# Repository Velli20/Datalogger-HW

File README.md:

# Datalogger board design with KiCad
The design files are available and free to use. For Any project related question do not hesitate to message me.

## Board Layout 3D View

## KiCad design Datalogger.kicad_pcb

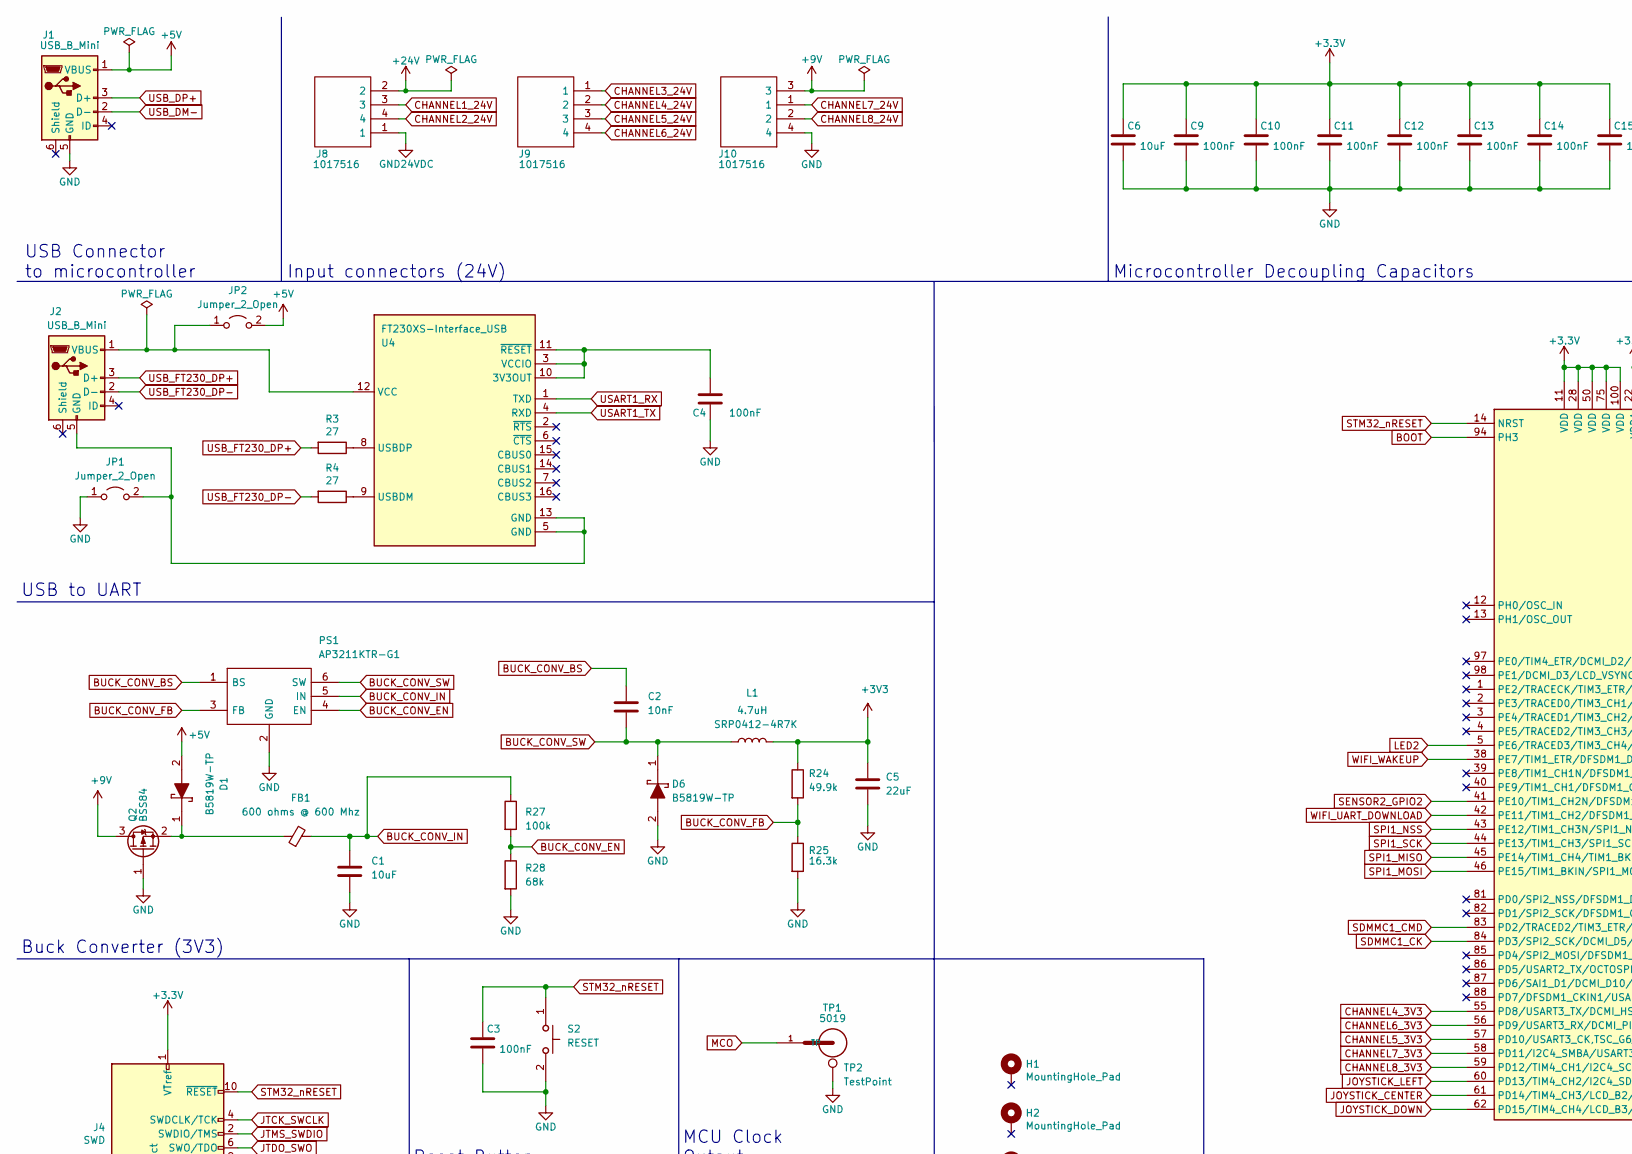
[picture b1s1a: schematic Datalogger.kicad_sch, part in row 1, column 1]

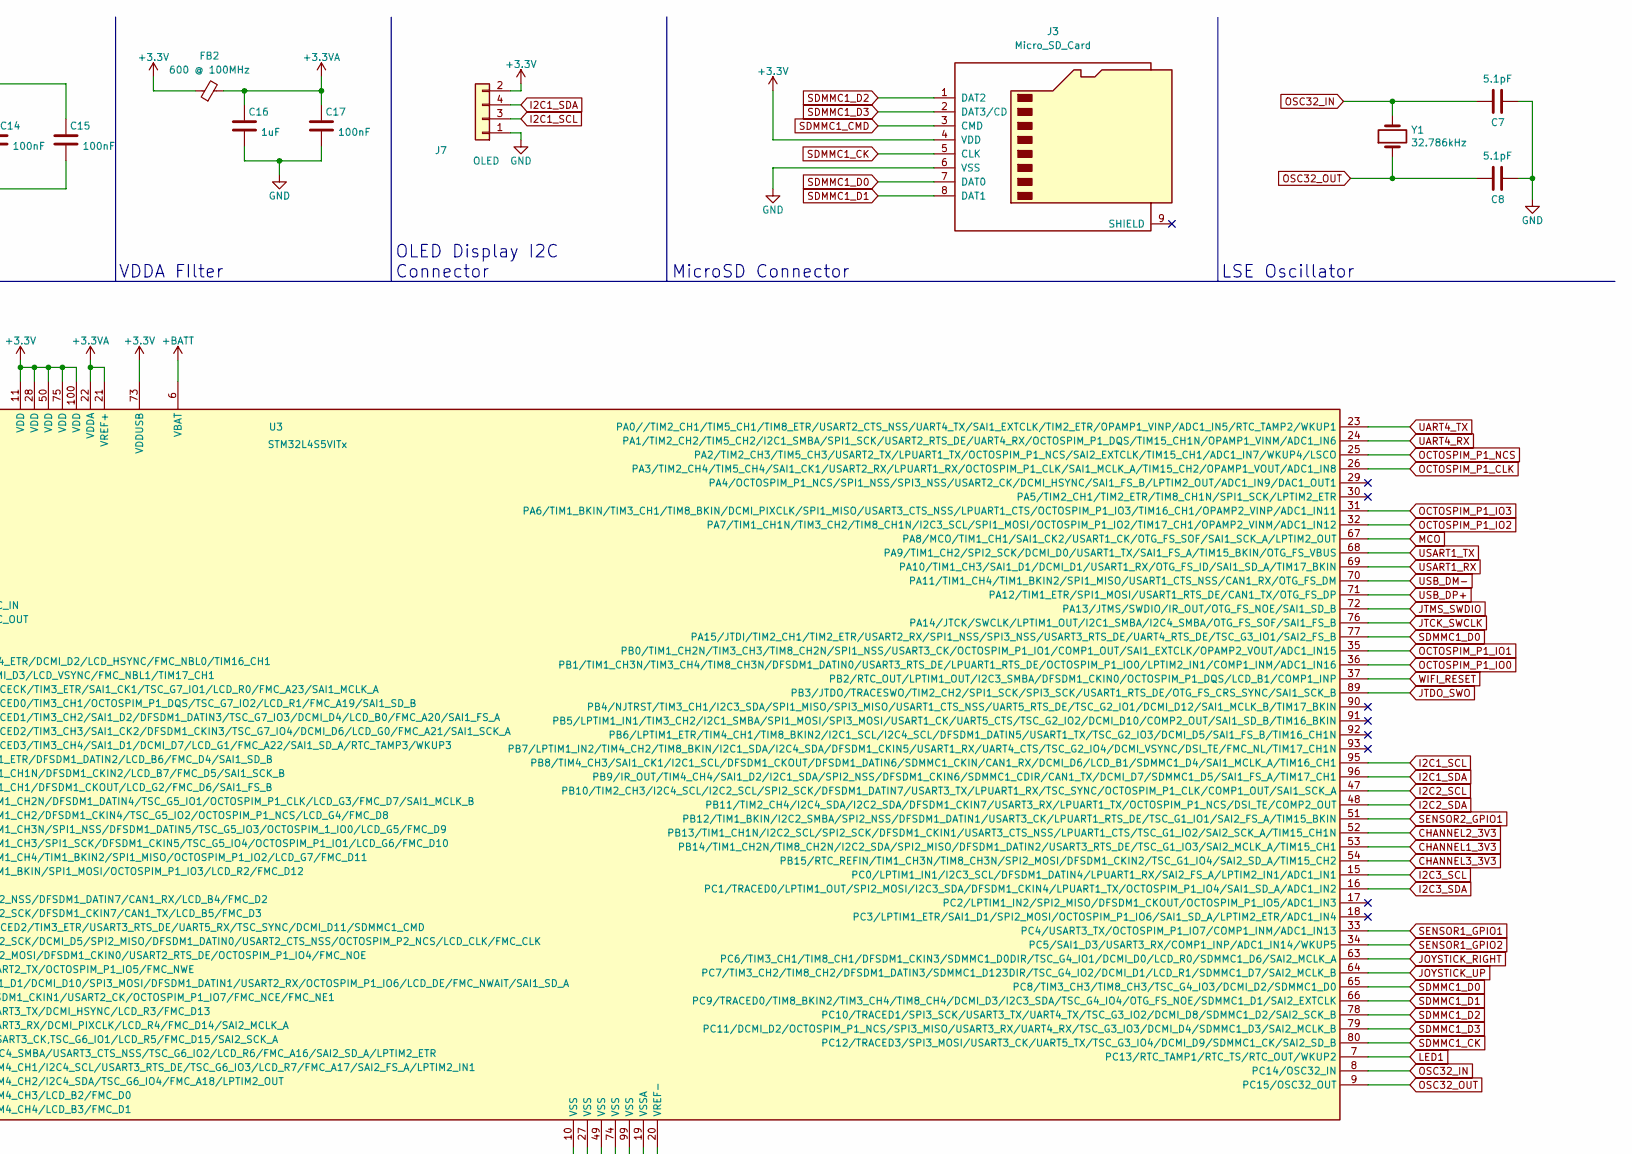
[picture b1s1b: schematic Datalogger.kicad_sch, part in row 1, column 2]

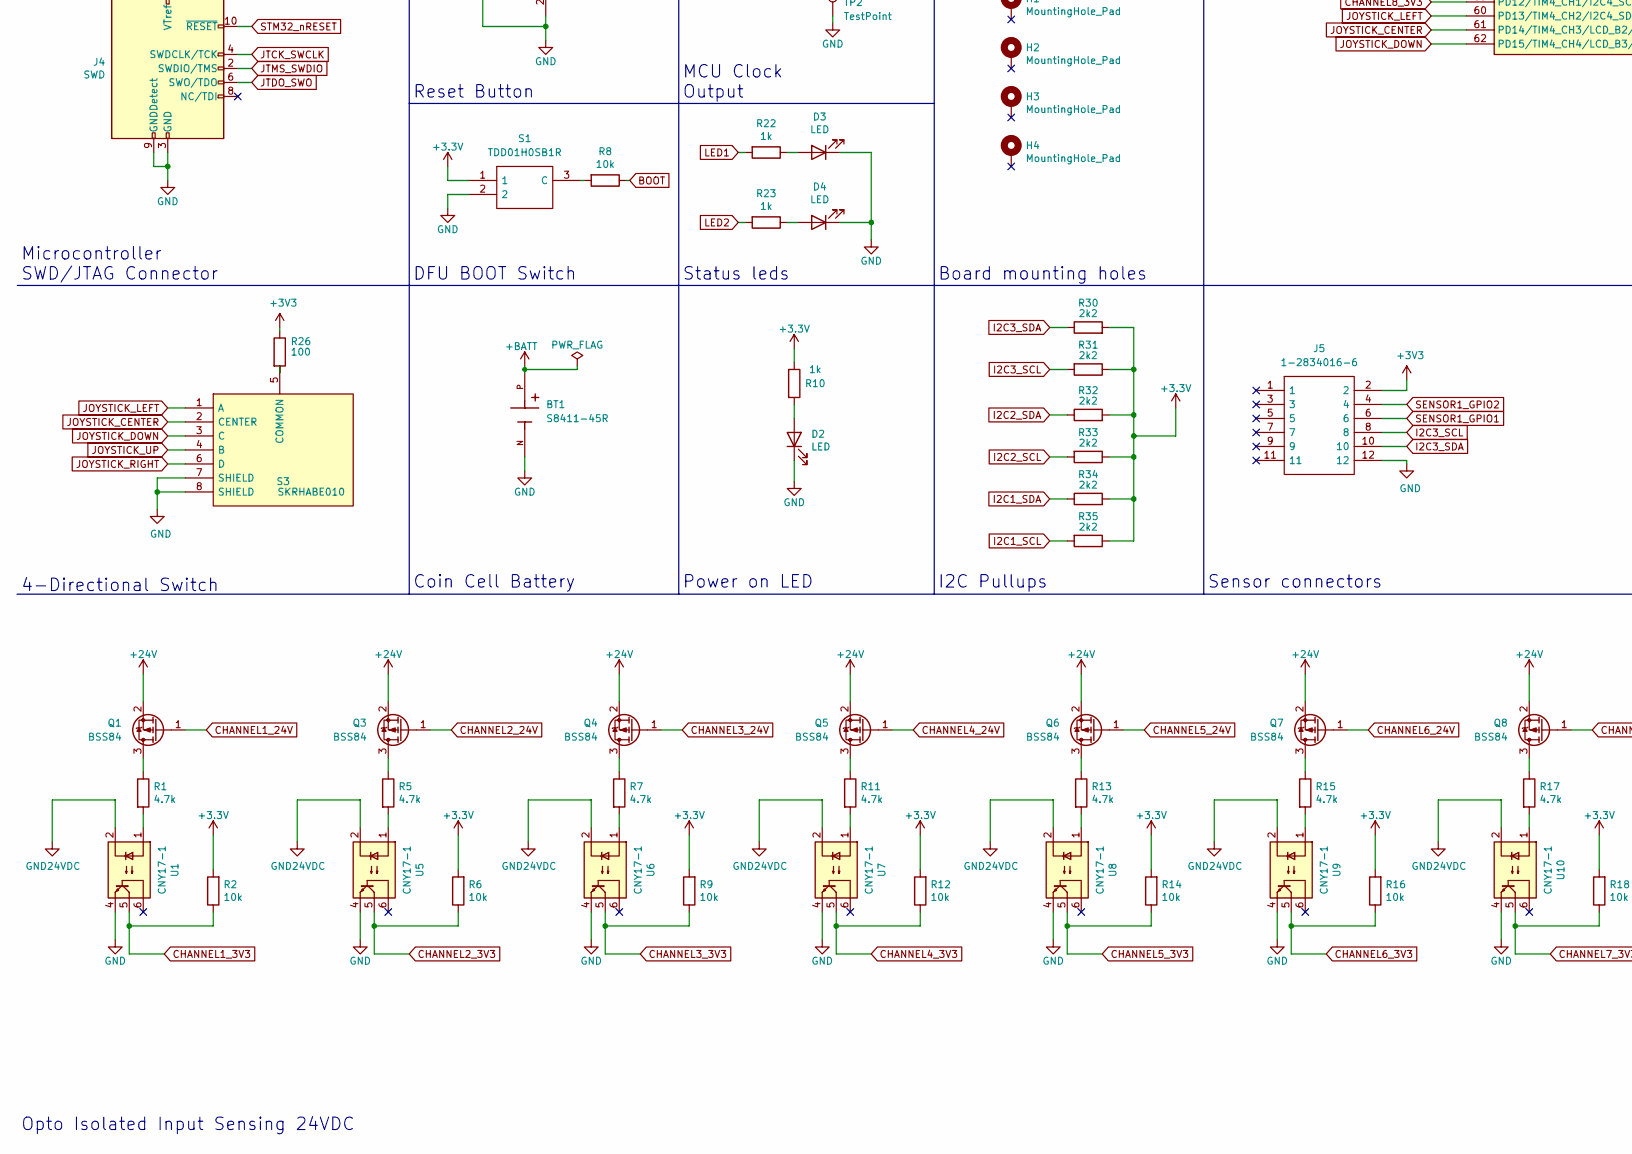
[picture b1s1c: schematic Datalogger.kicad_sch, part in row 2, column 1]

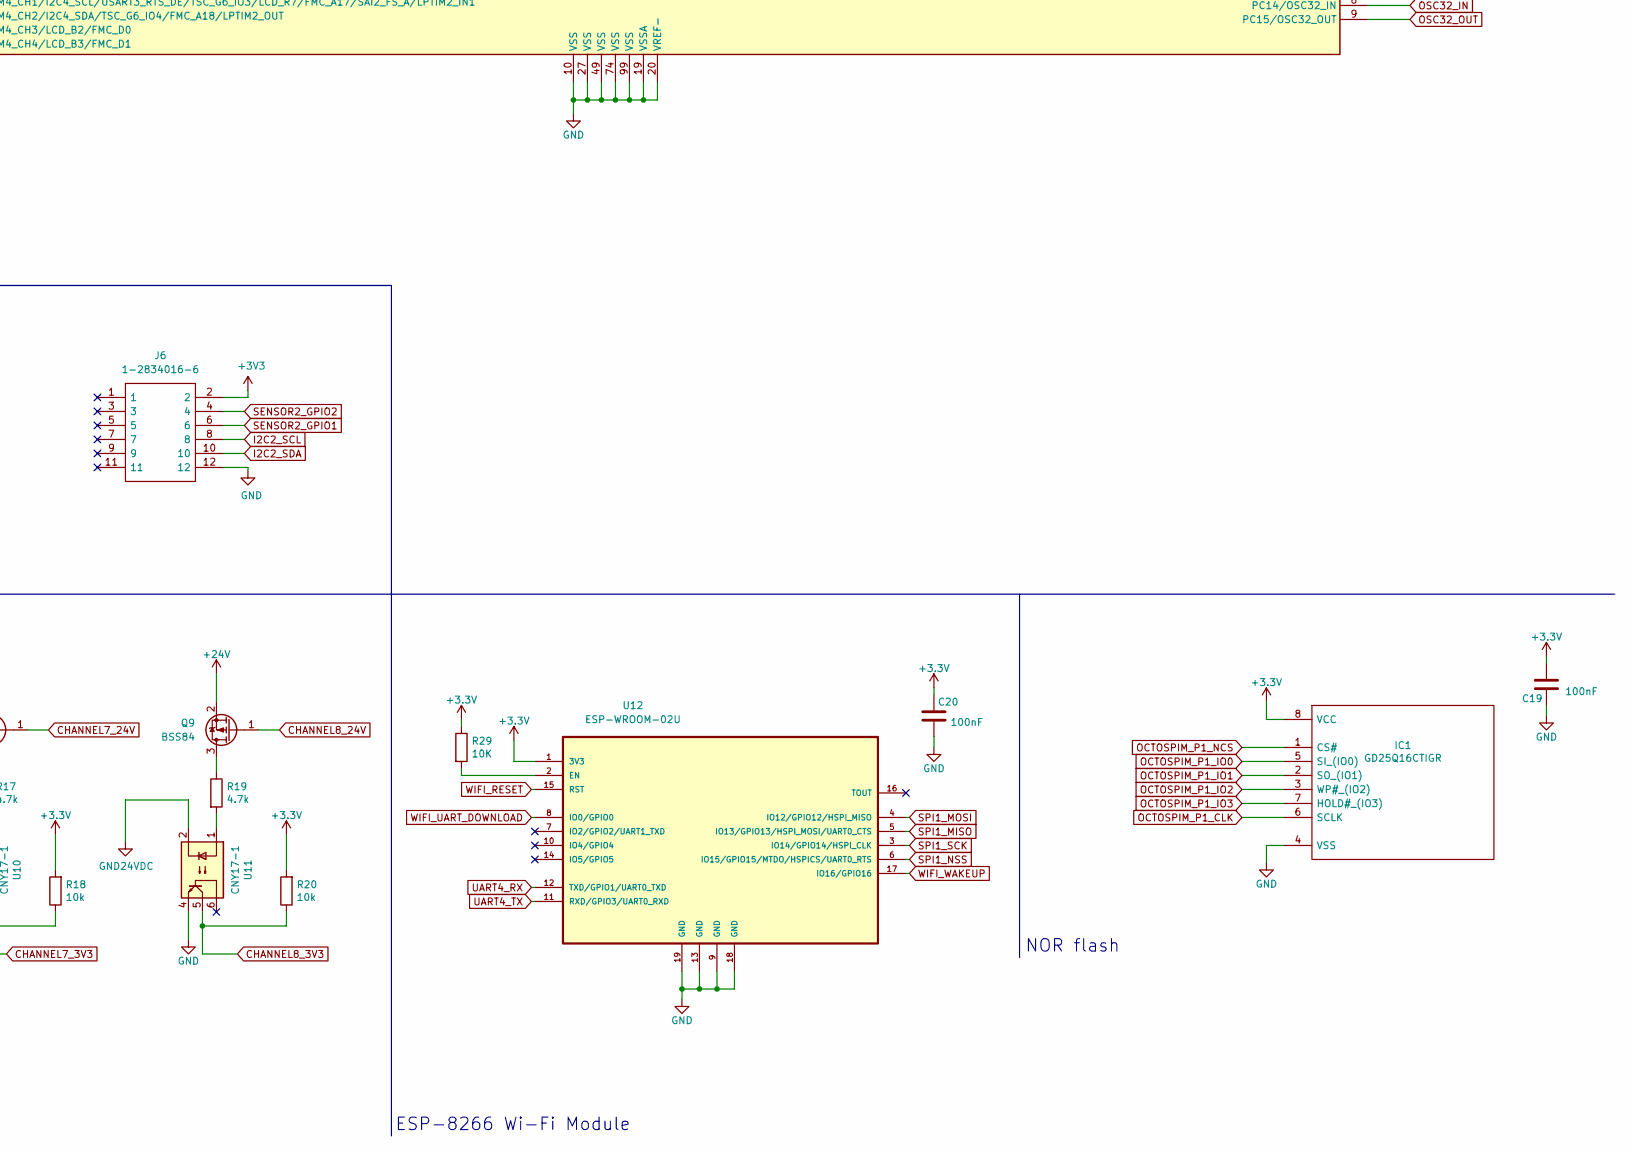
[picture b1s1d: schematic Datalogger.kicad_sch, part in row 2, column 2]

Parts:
BT1: S8411-45R; Harwin-S8411-45R
C1, C6: 10uF; C_0805_2012Metric
C2: 10nF; C_0805_2012Metric
C3, C4, C9, C10, C11, C12, C13, C14, C15, C17, C19, C20: 100nF; C_0603_1608Metric
C5: 22uF; C_0805_2012Metric
C7, C8: 5.1pF; C_0805_2012Metric
C16: 1uF; C_0603_1608Metric
D1, D6: B5819W-TP; Mouser Part Number 833-B5819W-TP
D2, D3, D4: LED; LED_0805_2012Metric
FB1: 600 ohms @ 600 Mhz; L_0805_2012Metric
FB2: 600 @ 100MHz; L_0603_1608Metric
H1, H2, H3, H4: MountingHole_Pad; MountingHole_3.7mm_Pad_Via
IC1: GD25Q16CTIGR; GD25Q127CSIGR; Manufacturer_Part_Number GD25Q16CTIGR
J1, J2: USB_B_Mini; USB_Micro-B_Molex-105017-0001
J3: Micro_SD_Card; Molex-104031-0811
J4: SWD; Harwin-M50-3610542R
J5, J6: 1-2834016-6; TE-Connectivity-1-2834016-6; Mouser Part Number 571-1-2834016-6
J7: OLED; SSD1306_Display_Module
J8, J9, J10: 1017516; Phoenix-Contact-1017516; Mouser Part Number 651-1017516
JP1, JP2: Jumper_2_Open; SolderJumper-2_P1.3mm_Open_Pad1.0x1.5mm
L1: 4.7uH; SRP04124R7K
PS1: AP3211KTR-G1; Mouser Part Number 621-AP3211KTR-G1
Q1, Q2, Q3, Q4, Q5, Q6, Q7, Q8, Q9: BSS84; SOT-23
R1, R5, R7, R11, R13, R15, R17, R19: 4.7k; R_0805_2012Metric
R2, R6, R8, R9, R12, R14, R16, R18, R20: 10k; R_0603_1608Metric
R3, R4: 27; R_0603_1608Metric
R10, R22, R23: 1k; R_0805_2012Metric
R24: 49.9k; R_0805_2012Metric
R25: 16.3k; R_0805_2012Metric
R26: 100; R_0603_1608Metric
R27: 100k; R_0805_2012Metric
R28: 68k; R_0805_2012Metric
R29: 10K; R_0603_1608Metric
R30, R31, R32, R33, R34, R35: 2k2; R_0603_1608Metric
S1: TDD01H0SB1R; Manufacturer_Part_Number TDD01H0SB1R; Mouser Part Number 611-TDD01H0SB1R
S2: RESET; TLSA100JLFS; Manufacturer_Part_Number TLS A 070 T3J LFS
S3: SKRHABE010; Mouser Part Number 688-SKRHAB
TP1: 5019; Keystone-5019
TP2: TestPoint; TestPoint_Pad_D3.0mm
U1, U5, U6, U7, U8, U9, U10, U11: CNY17-1; CNY17-4X009T
U3: STM32L4S5VITx; LQFP-100_14x14mm_P0.5mm
U4: FT230XS-Interface_USB; SSOP-16_3.9x4.9mm_P0.635mm
U12: ESP-WROOM-02U; PARTREV 1.1
Y1: 32.786kHz; ECS-327-7-16-C-TR

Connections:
+3.3VA: C16.1, C17.1, FB2.2, U3.21 (VREF+), U3.22 (VDDA)
+5V: D1.2, J1.1 (VBUS), JP2.2 (B)
+9V: J10.3, Q2.3 (D)
+24V: J8.2, Q1.2 (S), Q3.2 (S), Q4.2 (S), Q5.2 (S), Q6.2 (S), Q7.2 (S), Q8.2 (S), Q9.2 (S)
+BATT: BT1.P, U3.6 (VBAT)
BOOT: R8.1, U3.94 (PH3)
BUCK_CONV_BS: C2.1, PS1.1 (BS)
BUCK_CONV_EN: PS1.4 (EN), R27.2, R28.1
BUCK_CONV_FB: PS1.3 (FB), R24.2, R25.1
BUCK_CONV_IN: C1.1, FB1.2, PS1.5 (IN), R27.1
BUCK_CONV_SW: C2.2, D6.1, L1.1, PS1.6 (SW)
CHANNEL1_3V3: R2.1, U1.5, U3.53 (PB14/TIM1_CH2N/TIM8_CH2N/I2C2_SDA/SPI2_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)
CHANNEL1_24V: J8.3, Q1.1 (G)
CHANNEL2_3V3: R6.1, U3.52 (PB13/TIM1_CH1N/I2C2_SCL/SPI2_SCK/DFSDM1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), U5.5
CHANNEL2_24V: J8.4, Q3.1 (G)
CHANNEL3_3V3: R9.1, U3.54 (PB15/RTC_REFIN/TIM1_CH3N/TIM8_CH3N/SPI2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), U6.5
CHANNEL3_24V: J9.1, Q4.1 (G)
CHANNEL4_3V3: R12.1, U3.55 (PD8/USART3_TX/DCMI_HSYNC/LCD_R3/FMC_D13), U7.5
CHANNEL4_24V: J9.2, Q5.1 (G)
CHANNEL5_3V3: R14.1, U3.57 (PD10/USART3_CK,TSC_G6_IO1/LCD_R5/FMC_D1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), U8.5
CHANNEL5_24V: J9.3, Q6.1 (G)
CHANNEL6_3V3: R16.1, U3.56 (PD9/USART3_RX/DCMI_PIXCLK/LCD_R4/FMC_D1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), U9.5
CHANNEL6_24V: J9.4, Q7.1 (G)
CHANNEL7_3V3: R18.1, U3.58 (PD11/I2C4_SMBA/USART3_CTS_NSS/TSC_G6_IO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), U10.5
CHANNEL7_24V: J10.1, Q8.1 (G)
CHANNEL8_3V3: R20.1, U3.59 (PD12/TIM4_CH1/I2C4_SCL/USART3_RTS_DE/TS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), U11.5
CHANNEL8_24V: J10.2, Q9.1 (G)
GND: BT1.N, C1.2, C3.2, C4.1, C5.2, C6.2, C7.1, C8.1, C9.2, C10.2, C11.2, C12.2, C13.2, C14.2, C15.2, C16.2, C17.2, C19.1, C20.2, D2.1 (K), D3.1 (K), D4.1 (K), D6.2, IC1.4 (VSS), J1.5 (GND), J3.6 (VSS), J4.3 (GND), J4.5 (GND), J4.9 (GNDDetect), J5.12, J6.12, J7.1, J10.4, JP1.1 (A), PS1.2 (GND), Q2.1 (G), R25.2, R28.2, S1.2, S2.2, S3.7 (SHIELD), S3.8 (SHIELD), TP2.1, U1.4, U3.10 (VSS), U3.19 (VSSA), U3.20 (VREF-), U3.27 (VSS), U3.49 (VSS), U3.74 (VSS), U3.99 (VSS), U5.4, U6.4, U7.4, U8.4, U9.4, U10.4, U11.4, U12.9 (GND), U12.13 (GND), U12.18 (GND), U12.19 (GND)
GND1: J8.1, U1.2, U5.2, U6.2, U7.2, U8.2, U9.2, U10.2, U11.2
I2C1_SCL: J7.3, R35.2, U3.95 (PB8/TIM4_CH3/SAI1_CK1/I2C1_SCL/DFSDM1_C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)
I2C1_SDA: J7.4, R34.1, U3.96 (PB9/IR_OUT/TIM4_CH4/SAI1_D2/I2C1_SDA/SP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)
I2C2_SCL: J6.8, R33.2, U3.47 (PB10/TIM2_CH3/I2C4_SCL/I2C2_SCL/SPI2_SC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)
I2C2_SDA: J6.10, R32.1, U3.48 (PB11/TIM2_CH4/I2C4_SDA/I2C2_SDA/DFSDM1_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)
I2C3_SCL: J5.8, R31.2, U3.15 (PC0/LPTIM1_IN1/I2C3_SCL/DFSDM1_DATIN4/L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)
I2C3_SDA: J5.10, R30.1, U3.16 (PC1/TRACED0/LPTIM1_OUT/SPI2_MOSI/I2C3_S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)
JOYSTICK_CENTER: S3.2 (CENTER), U3.61 (PD14/TIM4_CH3/LCD_B2/FMC_D0)
JOYSTICK_DOWN: S3.3 (C), U3.62 (PD15/TIM4_CH4/LCD_B3/FMC_D1)
JOYSTICK_LEFT: S3.1 (A), U3.60 (PD13/TIM4_CH2/I2C4_SDA/TSC_G6_IO4/FMC_A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)
JOYSTICK_RIGHT: S3.6 (D), U3.63 (PC6/TIM3_CH1/TIM8_CH1/DFSDM1_CKIN3/SDMM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)
JOYSTICK_UP: S3.4 (B), U3.64 (PC7/TIM3_CH2/TIM8_CH2/DFSDM1_DATIN3/SDM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)
JTCK_SWCLK: J4.4 (SWDCLK/TCK), U3.76 (PA14/JTCK/SWCLK/LPTIM1_OUT/I2C1_SMBA/I2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)
JTDO_SWO: J4.6 (SWO/TDO), U3.89 (PB3/JTDO/TRACESWO/TIM2_CH2/SPI1_SCK/SPI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)
JTMS_SWDIO: J4.2 (SWDIO/TMS), U3.72 (PA13/JTMS/SWDIO/IR_OUT/OTG_FS_NOE/SAI1_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)
LED1: R22.2, U3.7 (PC13/RTC_TAMP1/RTC_TS/RTC_OUT/WKUP2)
LED2: R23.2, U3.5 (PE6/TRACED3/TIM3_CH4/SAI1_D1/DCMI_D7/LC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)
MCO: TP1.1 (TP), U3.67 (PA8/MCO/TIM1_CH1/SAI1_CK2/USART1_CK/OTG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)
unnamed: C4.2, U4.3 (VCCIO), U4.10 (3V3OUT), U4.11 (~RESET)
unnamed: D1.1, FB1.1, Q2.2 (S)
unnamed: D2.2 (A), R10.2
unnamed: D3.2 (A), R22.1
unnamed: D4.2 (A), R23.1
unnamed: Q1.3 (D), R1.1
unnamed: Q3.3 (D), R5.1
unnamed: Q4.3 (D), R7.1
unnamed: Q5.3 (D), R11.1
unnamed: Q6.3 (D), R13.1
unnamed: Q7.3 (D), R15.1
unnamed: Q8.3 (D), R17.1
unnamed: Q9.3 (D), R19.1
unnamed: R1.2, U1.1
unnamed: R3.1, U4.8 (USBDP)
unnamed: R4.1, U4.9 (USBDM)
unnamed: R5.2, U5.1
unnamed: R7.2, U6.1
unnamed: R8.2, S1.3 (C)
unnamed: R11.2, U7.1
unnamed: R13.2, U8.1
unnamed: R15.2, U9.1
unnamed: R17.2, U10.1
unnamed: R19.2, U11.1
unnamed: R26.2, S3.5 (COMMON)
unnamed: R29.2, U12.2 (EN)
unnamed: J2.1 (VBUS), JP2.1 (A), U4.12 (VCC)
unnamed: J2.5 (GND), JP1.2 (B), U4.5 (GND), U4.13 (GND)
OCTOSPIM_P1_CLK: IC1.6 (SCLK), U3.26 (PA3/TIM2_CH4/TIM5_CH4/SAI1_CK1/USART2_R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)
OCTOSPIM_P1_IO0: IC1.5 (SI_(IO0)), U3.36 (PB1/TIM1_CH3N/TIM3_CH4/TIM8_CH3N/DFSDM1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)
OCTOSPIM_P1_IO1: IC1.2 (SO_(IO1)), U3.35 (PB0/TIM1_CH2N/TIM3_CH3/TIM8_CH2N/SPI1_N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)
OCTOSPIM_P1_IO2: IC1.3 (WP#_(IO2)), U3.32 (PA7/TIM1_CH1N/TIM3_CH2/TIM8_CH1N/I2C3_S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)
OCTOSPIM_P1_IO3: IC1.7 (HOLD#_(IO3)), U3.31 (PA6/TIM1_BKIN/TIM3_CH1/TIM8_BKIN/DCMI_P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)
OCTOSPIM_P1_NCS: IC1.1 (CS#), U3.25 (PA2/TIM2_CH3/TIM5_CH3/USART2_TX/LPUART1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)
OSC32_IN: C7.2, U3.8 (PC14/OSC32_IN), Y1.2
OSC32_OUT: C8.2, U3.9 (PC15/OSC32_OUT), Y1.1
SDMMC1_CK: J3.5 (CLK), U3.80 (PC12/TRACED3/SPI3_MOSI/USART3_CK/UART5_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), U3.84 (PD3/SPI2_SCK/DCMI_D5/SPI2_MISO/DFSDM1_D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)
SDMMC1_CMD: J3.3 (CMD), U3.83 (PD2/TRACED2/TIM3_ETR/USART3_RTS_DE/UART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)
SDMMC1_D0: J3.7 (DAT0), U3.65 (PC8/TIM3_CH3/TIM8_CH3/TSC_G4_IO3/DCMI_D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), U3.77 (PA15/JTDI/TIM2_CH1/TIM2_ETR/USART2_RX/S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)
SDMMC1_D1: J3.8 (DAT1), U3.66 (PC9/TRACED0/TIM8_BKIN2/TIM3_CH4/TIM8_CH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)
SDMMC1_D2: J3.1 (DAT2), U3.78 (PC10/TRACED1/SPI3_SCK/USART3_TX/UART4_T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)
SDMMC1_D3: J3.2 (DAT3/CD), U3.79 (PC11/DCMI_D2/OCTOSPIM_P1_NCS/SPI3_MISO/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)
SENSOR1_GPIO1: J5.6, U3.33 (PC4/USART3_TX/OCTOSPIM_P1_IO7/COMP1_INM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)
SENSOR1_GPIO2: J5.4, U3.34 (PC5/SAI1_D3/USART3_RX/COMP1_INP/ADC1_IN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)
SENSOR2_GPIO1: J6.6, U3.51 (PB12/TIM1_BKIN/I2C2_SMBA/SPI2_NSS/DFSDM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)
SENSOR2_GPIO2: J6.4, U3.41 (PE10/TIM1_CH2N/DFSDM1_DATIN4/TSC_G5_IO1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)
SPI1_MISO: U3.45 (PE14/TIM1_CH4/TIM1_BKIN2/SPI1_MISO/OCTO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), U12.5 (IO13/GPIO13/HSPI_MOSI/UART0_CTS)
SPI1_MOSI: U3.46 (PE15/TIM1_BKIN/SPI1_MOSI/OCTOSPIM_P1_IO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), U12.4 (IO12/GPIO12/HSPI_MISO)
SPI1_NSS: U3.43 (PE12/TIM1_CH3N/SPI1_NSS/DFSDM1_DATIN5/T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), U12.6 (IO15/GPIO15/MTDO/HSPICS/UART0_RTS)
SPI1_SCK: U3.44 (PE13/TIM1_CH3/SPI1_SCK/DFSDM1_CKIN5/TSC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), U12.3 (IO14/GPIO14/HSPI_CLK)
STM32_nRESET: C3.1, J4.10 (~RESET), S2.1, U3.14 (NRST)
UART4_RX: U3.24 (PA1/TIM2_CH2/TIM5_CH2/I2C1_SMBA/SPI1_SC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), U12.12 (TXD/GPIO1/UART0_TXD)
UART4_TX: U3.23 (PA0//TIM2_CH1/TIM5_CH1/TIM8_ETR/USART2_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), U12.11 (RXD/GPIO3/UART0_RXD)
USART1_RX: U3.69 (PA10/TIM1_CH3/SAI1_D1/DCMI_D1/USART1_RX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), U4.1 (TXD)
USART1_TX: U3.68 (PA9/TIM1_CH2/SPI2_SCK/DCMI_D0/USART1_TX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), U4.4 (RXD)
USB_DM-: J1.2 (D-), U3.70 (PA11/TIM1_CH4/TIM1_BKIN2/SPI1_MISO/USAR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)
USB_DP+: J1.3 (D+), U3.71 (PA12/TIM1_ETR/SPI1_MOSI/USART1_RTS_DE/C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)
USB_FT230_DP+: J2.3 (D+), R3.2
USB_FT230_DP-: J2.2 (D-), R4.2
WIFI_RESET: U3.37 (PB2/RTC_OUT/LPTIM1_OUT/I2C3_SMBA/DFSDM1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), U12.15 (RST)
WIFI_UART_DOWNLOAD: U3.42 (PE11/TIM1_CH2/DFSDM1_CKIN4/TSC_G5_IO2/O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), U12.8 (IO0/GPIO0)
WIFI_WAKEUP: U3.38 (PE7/TIM1_ETR/DFSDM1_DATIN2/LCD_B6/FMC_D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), U12.17 (IO16/GPIO16)

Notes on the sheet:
Microcontroller SWD/JTAG Connector
Microcontroller Decoupling Capacitors
Status leds
I2C Pullups
Input connectors (24V)
DFU BOOT Switch
Board mounting holes
Opto Isolated Input Sensing 24VDC
VDDA FIlter
Power on LED
4-Directional Switch
MicroSD Connector
MCU Clock Output
USB Connector to microcontroller
NOR flash
Reset Button
USB to UART
Sensor connectors
LSE Oscillator
ESP-8266 Wi-Fi Module
Coin Cell Battery
OLED Display I2C Connector
Buck Converter (3V3)

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
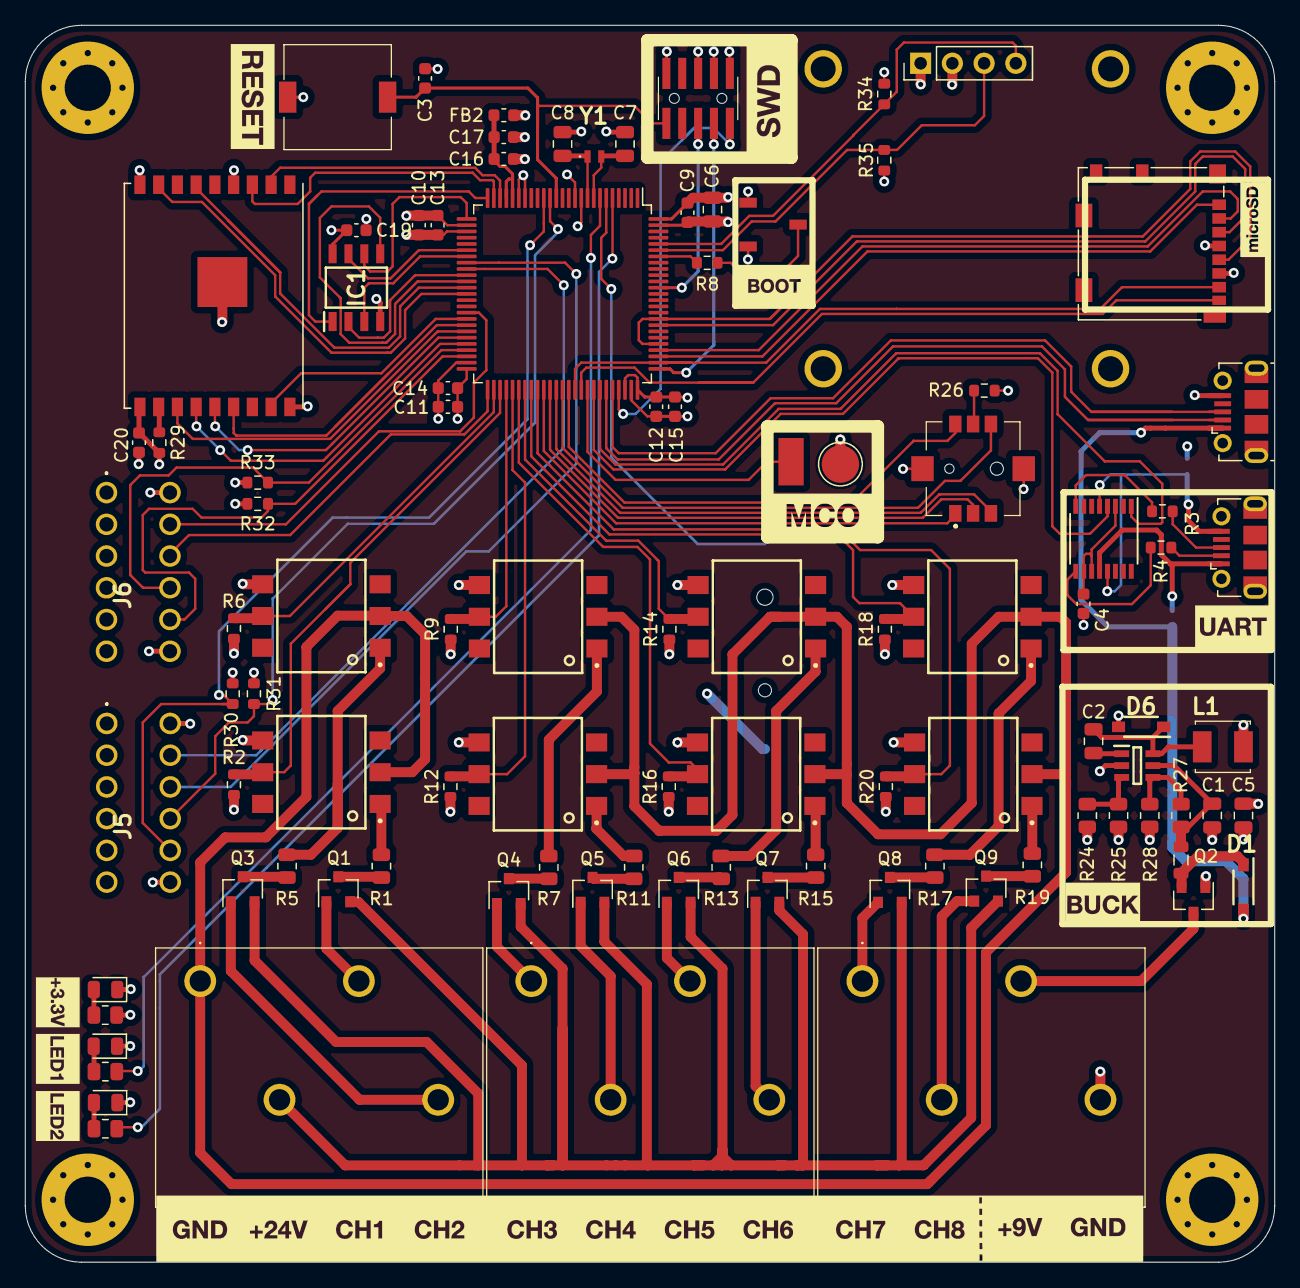
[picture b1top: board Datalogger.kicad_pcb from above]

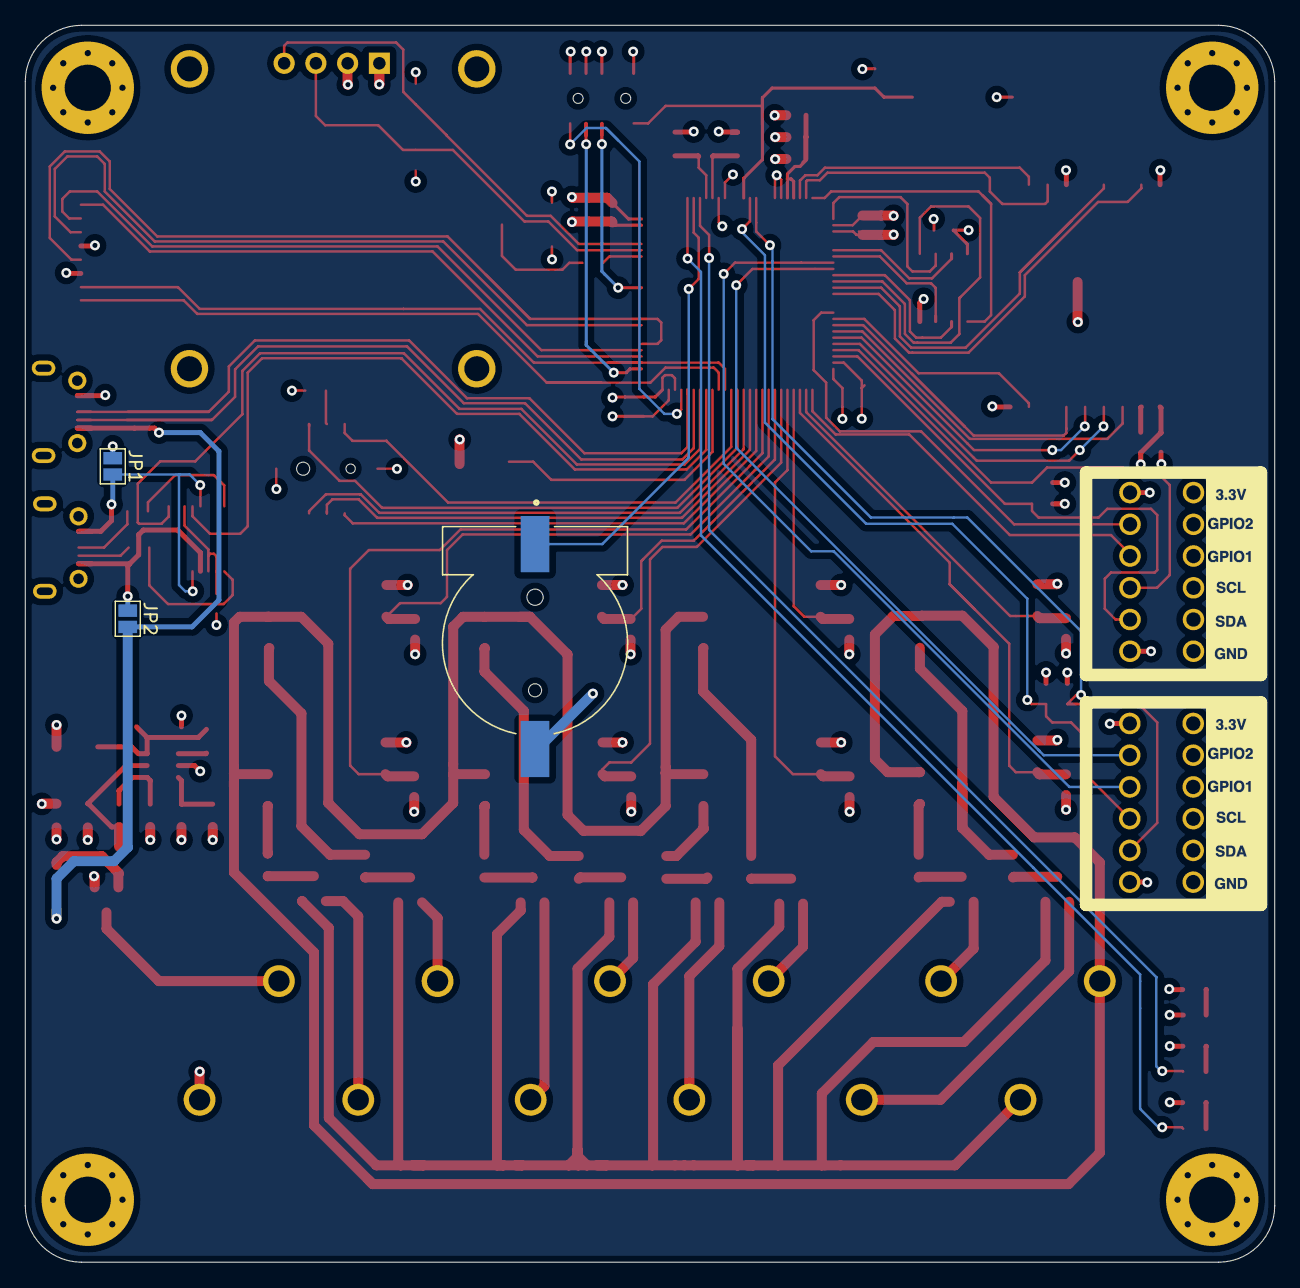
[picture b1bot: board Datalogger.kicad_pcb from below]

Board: 4 copper layers, 100.0 x 99.0 mm, 106 parts (3 on the bottom side), 109 nets.

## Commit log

2022-07-23 Rev 0.4
2022-08-06 Adds readme
